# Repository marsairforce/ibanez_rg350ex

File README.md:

# Ibanez RG350EX

An Ibanez RG350EX with Seymour Duncan Invader pickups and custom wiring.

These switches allow for me to have 20 different configurations of the two pickups

* Just one pickup
* Both pickups, in series or parallel
* Phase reversing of the pickups
* Coil splitting (series or parallel)

I posted this in hopes it will be interesting or thought provoking to other musicians. And to welcome feedback for ideas to improve things.

If anything else an instruction manual for myself so I can always remember how my guitar works.

## Background

I got this in 2009 from Fleet Pro sound. I think for what ever reason I was missing my Mexican Strat after I sold it before moving back to Winnipeg following the intern at Nortel. By now I was back in Ottawa and had wanted to get back into Guitar.

I tried to get into playing it but it sounded terrible.

So it sat in the furnace room for like a decade.

Now I brought it out, changed the pickups and the wiring and it is awesome again.

## Switch Function

There are eight switches on the control panel.

Seven of the switches work to change the pickup configuration.

The eigth switch is a cut out for the tone circuit.

(diagram not to scale)

* six toggle switches.
* two push pull switches on the potentiometers.

Table 1 below explains what each switch does.

| Switch | Description                | Up | Down |
|:-------|:---------------------------|:---|:-----|
| S1     | Phase invert bridge pickup | Neck pickup phase is inverted from the bridge pickup | Neck pickup phase is the same as the bridge pickup |
| S2     | Neck pickup high side      | Connected to bridge low side | Connected to output
| S3     | Neck pickup low side       | Connected to bridge high side | Connected to ground
| S4     | Bridge pickup high side    | Connected to neck pickup low side | Connected to output |
| S5     | Bridge pickup low side     | Connected to neck pickup high side | Connected to ground |
| S6     | Neck coil split            | Nck pickup in series (humbuck) mode | Neck pickup in single (parallel) coil mode |
| S7     | Bridge coil split          | Bridge pickup in series (humbuck) mode | Bridge pickup in single (parallel) coil mode |

And table 2 below explains the modes

There are 20 tone possibilities.

> This does not include the other permutation of having the pickups in series. The setup shown here with [S2, S4, S3, S5] i [D, U, U, D] has the bridge pickup connecting to the the output jack, then to the neck pickup, then to the ground.
>
> If we had [S2, S4, S3, S5] as [U, D, D, U] that would connect the bridge pickup to the output jack, then to the neck pickup, then to ground.
>
> However this is tonally identical, so the permutation was omitted.

## Schematic

For those interested.

The function of series/parallel for the pickups is done with S2, S3, S4, and S5. These are DPDT toggle switches, but I am only using 1 pole on each switch.

> This was just my idea for how to make two pick ups be
>
> * none
> * just one
> * just the other
> * both in parallel
> * both in series
>
> If you have any ideas for how I could do this better I am excited to learn.

The S6 and S7 used to be phase control switches. Where each pickup went into these to reverse the phase. I later realized that with only two pickups I do not require two switches. This was because my previous guitar had three pickups and I put in three phase switches, one for each pick up. But here with two pickups, if I move both switches the pick ups are just back in phase with each other again. So if I have only one switch then the pick ups will be out of phase, and it does not matter which pick up is the out of phase one. I moved the phase control switch to the S1 (the push/pull switch in the volume pot) and made these S6 and S7 be the coil split controls for each pickup.

I do not actually split the coils, just follow the Seymour Duncan wiring guide for series / parallel. Basically the white and red wires are not hard soldered to each other, but to the switch.

I wired the tone circuit to be a grease bucket tone mod (search the Internet). The S8 is not really needed if we crank the tone knob all the way off I find. I might rewire this later to do something else.

## Application

Some practical tone settings that are similar to other guitars or styles of playing.

| Mode                 | S1 | S2 | S3 | S4 | S5 | S6 | S7 | Notes |
|:---------------------|:--:|:--:|:--:|:--:|:--:|:--:|:--:|:------|
| A Stratocaster sound | D  | U  | D  | D  | D  | D  | D  | Just the bridge pick up, single coil mode |
| A Telecaster sound   | D  | D  | U  | D  | D  | D  | D  | Just the neck pickup, single coil mode |
| Heavy and Loud       | D  | D  | U  | U  | D  | U  | U  | Both pickups in humbuck mode and series |

I will expand the "sounds like a " table as I play with it more.

## Waveform Analysis

Hooking the guitar directly up to an oscilloscope.
Trying to strike the low E string the same way each time.

## Single Pickup

The main difference here is changing the single coil to double coils

| Pickup | Single coil | Humbucking | Change |
|:-----|:---------|:------|:--|
| **Bridge** |  |  | S7 |
| **Neck**   |  |  | S6 |

## Pickups in Parallel

| Phase | Neck (S) Bridge (S) | Neck (S) Bridge (H) | Neck (H) Bridge (S) | Neck (H) Bridge (H) |
|:-|:-|:-|:-|:-|
| **In Phase** |  |  |  |  |
| **Out Phase** |  |  |  |  |

## Pickups in Series

| Phase | Neck (S) Bridge (S) | Neck (S) Bridge (H) | Neck (H) Bridge (S) | Neck (H) Bridge (H) |
|:-|:-|:-|:-|:-|
| **In Phase** |  |  |  |  |
| **Out Phase** |  |  |  |  |

## Custom Aluminum Pick Guard

I removed the middle pick up. I did not have any use for it. This left a hole where the pick up used to be. I tried covering it with shiny furnace pipe tape. And later a piece of a CD-ROM. But no matter what i did it looked pretty Ghetto.

If I could have built a sustainer pickup it would have fit nicely into the slot. But I have not been able to overcome several technical challenges of making this work. Mostly the magnetic fields from the coil in middle position interfere with the other pickups.

So I took the plastic pick guard to a water jet cutting place in town and had them make me a pick guard out of 1/8" aluminum. It had the same holes as the switch configurations from before too.

I attached the pick guard using some hex cap machine bolts that attach to wood screw ancher nuts in the body. I had to drill out a larger hole to screw the nuts into the body.

I liked the effect so much I went and modified my Fender Squire bass to be the same as well. I don't have a project for the bass, it just follows the evolution of the guitar.

The result is something I think is very visually stunning but also provides a bit more of a resonance to the sound of the guitar, I think anyway.

## Clean Boost Circuit

I built a clean boost based on the TL071 op-amp inside the guitar.

It is powered by a stereo jack. The ring connector on the TRS connector can supply 9V into the guitar. An internal DC-DC converter steps it up to 12V. The gain is fixed to be just about 1:1.

The motivation here is not to produce a louder output, but to convert the high impedence from the pickups into a low impedence signal to drive over the patchcord.

Even with the 20 foot patch cord I regularly use I can slightly hear a difference with the tonal quality and the sustain of some higher pitched notes when using the clean boost vs not using the clean boost.

The clean boost circuit facilitated upgrading the jack connector. I got a really good Switchcraft model. Which randomly did not come with the mounting hardware. A trip to the hardware store found some more special ass nut to fit it. And then more drilling to make it fit. The jack now holds the patch cord very well. And being fully shielded is less interface to pick up noise like the old one was.

## Locking tuners

I replaced the stock tuners with locking tuners. These allow me to wind the strings a little easier without needing to wind the string around a bunch of times. I don't really need them with the locking nut, but I was curious what they were about. I also wanted to replace the standard tuners because several of them had a lot of random backlash and that made tuning somewhat challenging.

## Actual Floyd Rose Trem

I got tired of the shitty edge trem. The tremmolo bar was so loose it was not even useable. The shitty zinc block under it was not very tonally pleasing to me. And the edges of the metal of the bridge against the posts were all shitty and worn in. Because its a shitty bridge.

The actual floyd rose trem has a good feel to it, I think. I got the fat brass sustain block to go with it, so more of a different sound from that as well. I first ordered the 37mm block, but it was just a bit too big to allow me to ge the back cover onto the guitar, and would touch your body as you played. I later ordered a 32mm block.

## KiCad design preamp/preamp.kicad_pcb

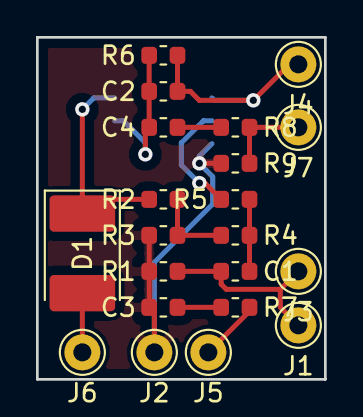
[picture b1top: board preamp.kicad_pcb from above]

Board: 2 copper layers, 16.0 x 19.0 mm, 22 parts (1 on the bottom side), 13 nets.

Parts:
C1: 0.1uF; C_0603_1608Metric
C2: 47pF; C_0603_1608Metric
C3: 4.7uF; C_0603_1608Metric
C4: 15uF; C_0603_1608Metric
D1: D; D_2114_3652Metric_Castellated
J1: From Volume Knob; Pin_D1.0mm_L10.0mm
J2: GND; Pin_D1.0mm_L10.0mm
J3: Bypass SW; Pin_D1.0mm_L10.0mm
J4: RV1; Pin_D1.0mm_L10.0mm
J5: RV2; Pin_D1.0mm_L10.0mm
J6: 9V; Pin_D1.0mm_L10.0mm
J7: Audio Out; Pin_D1.0mm_L10.0mm
R1: 22M; R_0603_1608Metric
R2, R3: 100K; R_0603_1608Metric
R4: 10M; R_0603_1608Metric
R5: 1K; R_0603_1608Metric
R6: 56K; R_0603_1608Metric
R7: 2.7K; R_0603_1608Metric
R8: 470; R_0603_1608Metric
R9: 16K; R_0603_1608Metric
U1: TL071; SOIC-8_3.9x4.9mm_P1.27mm

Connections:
GND: C3.2, J2.1, R1.2, R3.2, R9.2, U1.4
unnamed: C1.1, R4.1, R5.2
unnamed: C1.2, J1.1, J3.1, R1.1
unnamed: C2.1, C4.2, R6.1, U1.6
unnamed: C2.2, J4.1, R6.2, U1.2
unnamed: C3.1, R7.2
unnamed: C4.1, R8.2
unnamed: D1.1, R2.1, U1.7
unnamed: D1.2, J6.1
unnamed: J5.1, R7.1
unnamed: J7.1, R8.1, R9.1
unnamed: R2.2, R3.1, R4.2
unnamed: R5.1, U1.3

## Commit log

2019-02-19 create schematic for wiring
2019-02-21 Update schematic following coil split switch mod
2019-02-21 Add link to wiring diagram for series/parallel switch
2019-02-25 update schematic. add pictures
2019-02-25 Bug fix typos
2019-02-25 replace switch functions with markdown table.
2019-02-25 Add waveform analysis
2019-02-25 github md fix
2019-02-25 add build photos
2019-05-03 local mods, was updating wiring
2019-05-03 create a preamp module
2019-05-03 nodes on tuning pegs
2019-06-03 preamp module
2019-06-03 update documentation
